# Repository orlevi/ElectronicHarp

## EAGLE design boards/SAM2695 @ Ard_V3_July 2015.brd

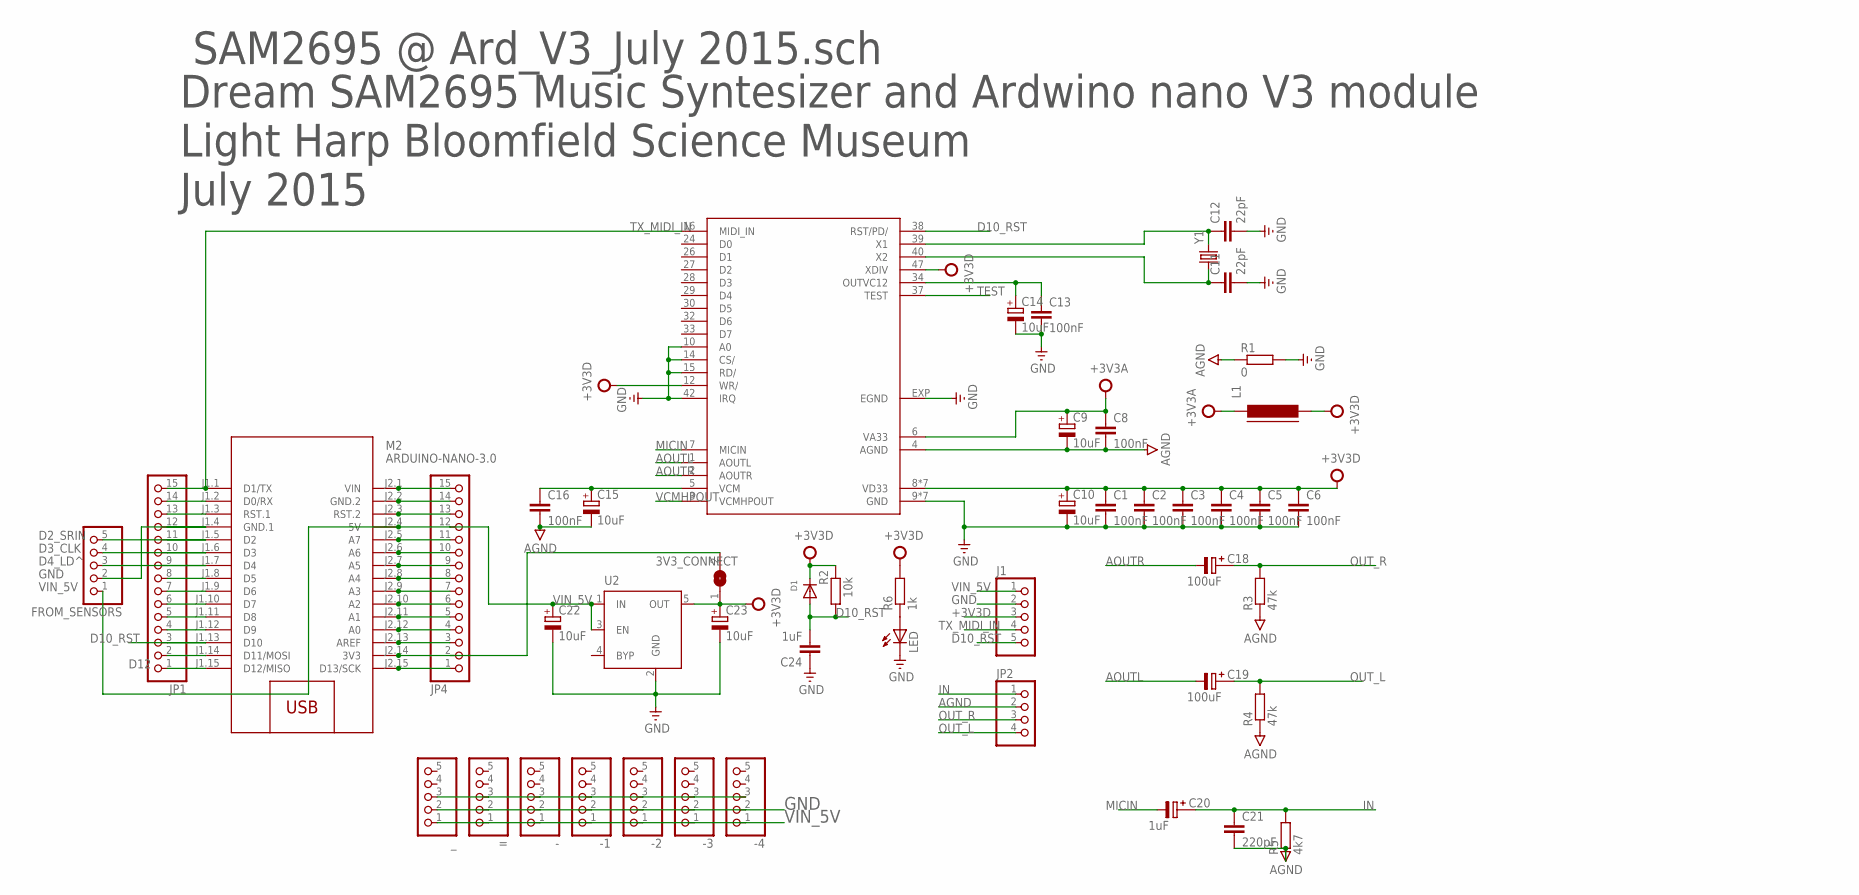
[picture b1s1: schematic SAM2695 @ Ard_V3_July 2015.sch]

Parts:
3V3_CONNECT: SJ
-, -1, -2, -3, -4: PIN_HEAD_1X5_MARKED; 1X5_MARKED
=: PIN_HEAD_1X5_MARKED; 1X5_MARKED
C1, C2, C3, C4, C5, C6, C8, C13, C16: 100nF; C0603K
C9, C10, C14, C15, C22, C23: 10uF; A/3216-18R
C11, C12: 22pF; C0603K
C18, C19: 100uF; SV-B
C20: 1uF; SV-B
C21: 220pF; C0603K
C24: 1uF; C0603
D1: DIODESOD-123; SOD-123
FROM_SENSORS: PIN_HEAD_1X5_MARKED; 1X5_MARKED
J1: PIN_HEAD_1X5_MARKED; 1X5_MARKED
JP1, JP4: PINHD-1X15; 1X15
JP2: HEADER-1X4ROUND; 1X04_ROUND
L1: FERRITE-0603; FB603
LED: LEDCHIP-LED0603; CHIP-LED0603
M2: ARDUINO-NANO-3.0
R1: 0; R0603
R2: 10k; R0603
R3, R4: 47k; R0603
R5: 4k7; R0603
R6: 1k; R0603
U2: MIC5219XX; SOT23-5
U$2: SAM2695LONG_PAD; QFN48_LONG_PAD
Y1: CRYSTALTXC-7A; CRYSTAL-TXC-7A
_: PIN_HEAD_1X5_MARKED; 1X5_MARKED

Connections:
+3V3A: C8.1, C9.+, L1.1, U$2.6 (VA33)
+3V3D: 3V3_CONNECT.1, C1.1, C2.1, C3.1, C4.1, C5.1, C6.1, C10.+, C23.+, D1.C, J1.3, L1.2, R2.2, R6.2, U2.5 (OUT), U$2.8 (VD33), U$2.11 (VD33), U$2.12 (WR/), U$2.20 (VD33), U$2.31 (VD33), U$2.35 (VD33), U$2.41 (VD33), U$2.46 (VD33), U$2.47 (XDIV)
AGND: C8.2, C9.-, C15.-, C16.2, C21.2, JP2.2, R1.1, R3.1, R4.1, R5.1, U$2.4 (AGND)
AOUTL: C19.-, U$2.1 (AOUTL)
AOUTR: C18.-, U$2.2 (AOUTR)
D2_SRIN: FROM_SENSORS.5, JP1.11, M2.J1.5 (D2)
D3_CLK: FROM_SENSORS.4, JP1.10, M2.J1.6 (D3)
D4_LD^: FROM_SENSORS.3, JP1.9, M2.J1.7 (D4)
D5: JP1.8, M2.J1.8 (D5)
D6: JP1.7, M2.J1.9 (D6)
D7: JP1.6, M2.J1.10 (D7)
D8: JP1.5, M2.J1.11 (D8)
D9: JP1.4, M2.J1.12 (D9)
D10_RST: C24.2, D1.A, J1.5, JP1.3, M2.J1.13 (D10), R2.1, U$2.38 (RST/PD/)
D11: JP1.2, M2.J1.14 (D11/MOSI)
D12: JP1.1, M2.J1.15 (D12/MISO)
D13: JP4.1, M2.J2.15 (D13/SCK)
GND: -.2, -1.2, -2.2, -3.2, -4.2, =.2, C1.2, C2.2, C3.2, C4.2, C5.2, C6.2, C10.-, C11.2, C12.2, C13.2, C14.-, C22.-, C23.-, C24.1, FROM_SENSORS.2, J1.2, JP1.12, JP4.14, LED.C, M2.J1.4 (GND.1), M2.J2.2 (GND.2), R1.2, U2.2 (GND), U$2.9 (GND), U$2.10 (A0), U$2.13 (GND), U$2.14 (CS/), U$2.15 (RD/), U$2.18 (GND), U$2.25 (GND), U$2.36 (GND), U$2.42 (IRQ), U$2.45 (GND), U$2.48 (GND), U$2.EXP (EGND), _.2
IN: C20.+, C21.1, JP2.1, R5.2
MICIN: C20.-, U$2.7 (MICIN)
unnamed: -.3, -1.3, -2.3, -3.3, -4.3, =.3, _.3
unnamed: C13.1, C14.+, U$2.34 (OUTVC12)
unnamed: C12.1, U$2.39 (X1), Y1.P$2 (2)
unnamed: C11.1, U$2.40 (X2), Y1.P$1 (1)
unnamed: LED.A, R6.1
unnamed: C15.+, C16.1, U$2.5 (VCM)
unnamed: 3V3_CONNECT.2, JP4.2, M2.J2.14 (3V3)
unnamed: JP4.3, M2.J2.13 (AREF)
unnamed: JP4.4, M2.J2.12 (A0)
unnamed: JP4.5, M2.J2.11 (A1)
unnamed: JP4.6, M2.J2.10 (A2)
unnamed: JP4.7, M2.J2.9 (A3)
unnamed: JP4.8, M2.J2.8 (A4)
unnamed: JP4.9, M2.J2.7 (A5)
unnamed: JP4.10, M2.J2.6 (A6)
unnamed: JP4.11, M2.J2.5 (A7)
unnamed: JP4.15, M2.J2.1 (VIN)
OUT_L: C19.+, JP2.4, R4.2
OUT_R: C18.+, JP2.3, R3.2
RST1_ARD: JP1.13, M2.J1.3 (RST.1)
RST2_ARD: JP4.13, M2.J2.3 (RST.2)
RX: JP1.14, M2.J1.2 (D0/RX)
TEST: U$2.37 (TEST)
TX_MIDI_IN: J1.4, JP1.15, M2.J1.1 (D1/TX), U$2.16 (MIDI_IN)
VCMHPOUT: U$2.3 (VCMHPOUT)
VIN_5V: -.1, -1.1, -2.1, -3.1, -4.1, =.1, C22.+, FROM_SENSORS.1, J1.1, JP4.12, M2.J2.4 (5V), U2.1 (IN), U2.3 (EN), _.1

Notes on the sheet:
SAM2695 @ Ard_V3_July 2015.sch
Dream SAM2695 Music Syntesizer and Ardwino nano V3 module Light Harp Bloomfield Science Museum July 2015

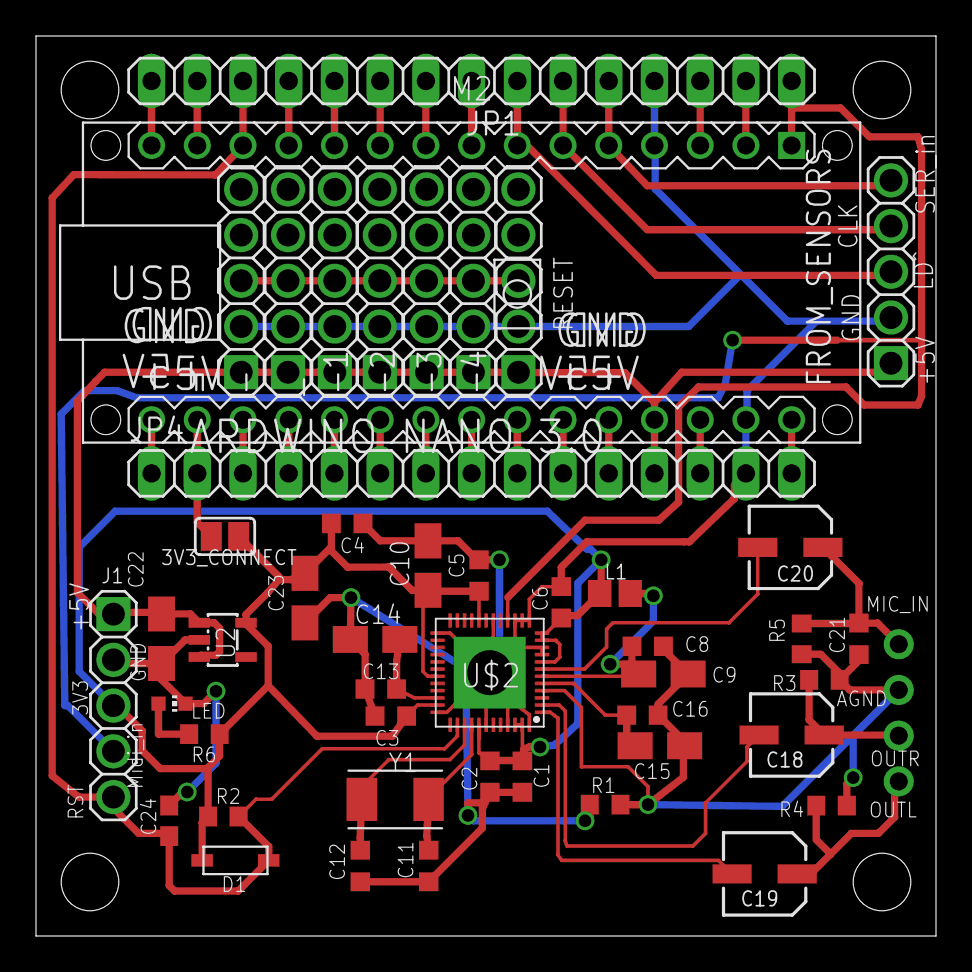
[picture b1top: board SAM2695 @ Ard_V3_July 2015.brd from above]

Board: 2 copper layers, 50.0 x 50.0 mm, 48 parts (0 on the bottom side), 44 nets.

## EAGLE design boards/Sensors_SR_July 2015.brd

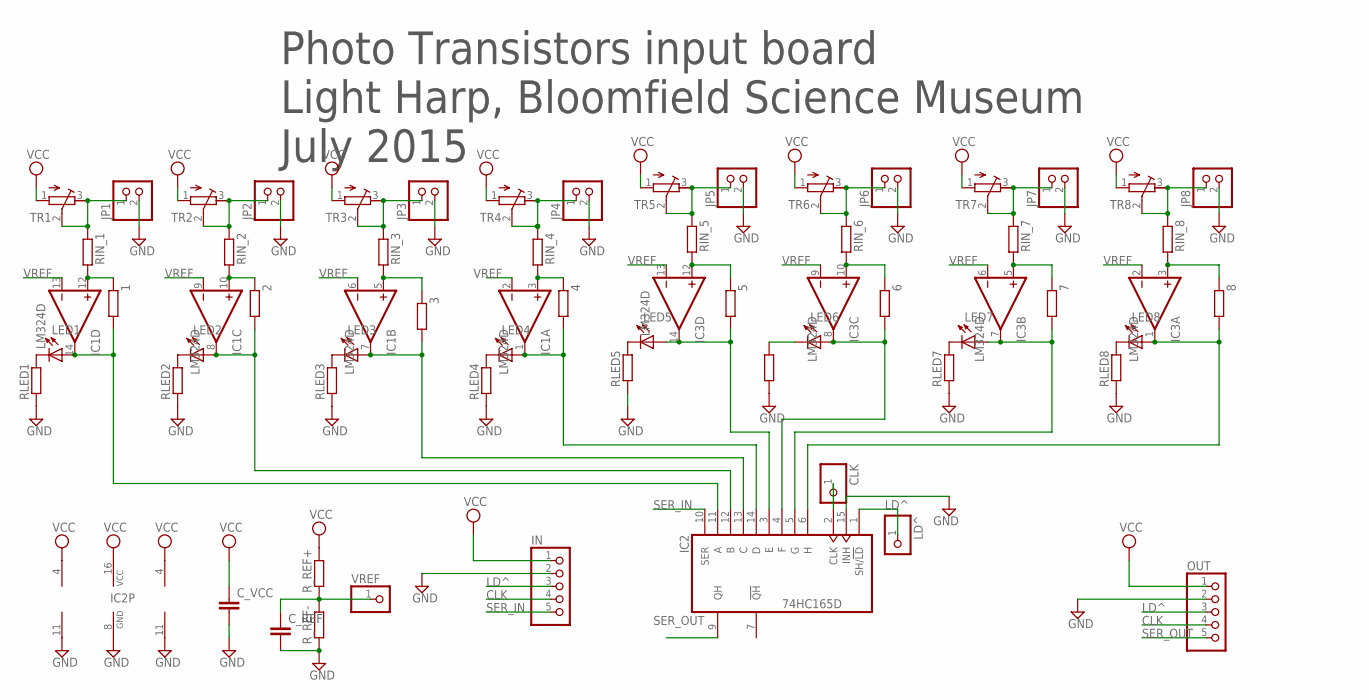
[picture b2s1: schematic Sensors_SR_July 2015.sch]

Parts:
1, 2, 3, 4, 5, 6, 7, 8: R-EU_R0603; R0603
CLK: PINHD-1X1; 1X01
C_REF: C-EUC0603; C0603
C_VCC: C-EUC0805; C0805
IC1, IC3: LM324D; SO14
IC2: 74HC165D; SO16
IN: PIN_HEAD_1X5_MARKED; 1X5_MARKED
JP1, JP2, JP3, JP4, JP5, JP6, JP7, JP8: PINHD-1X2SQ&RND; 1X02_SQ&ROUND
LD^: PINHD-1X1; 1X01
LED1, LED2, LED3, LED4, LED5, LED6, LED7, LED8: LEDCHIPLED_0805; CHIPLED_0805
OUT: PIN_HEAD_1X5_MARKED; 1X5_MARKED
RIN_1, RIN_2, RIN_3, RIN_4, RIN_5, RIN_6, RIN_7, RIN_8: R-EU_R0603; R0603
RLED1, RLED2, RLED3, RLED4, RLED5, RLED6, RLED7, RLED8: R-EU_R0603; R0603
R_REF+: R-EU_R0603; R0603
R_REF-: R-EU_R0603; R0603
TR1, TR2, TR3, TR4, TR5, TR6, TR7, TR8: R-TRIMM64W_W; RTRIM64W_W
VREF: PINHD-1X1; 1X01

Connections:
CLK: CLK.1, IC2.2 (CLK), IN.4, OUT.4
GND: C_REF.2, C_VCC.2, IC1.11 (V-), IC2.8 (GND), IC2.15 (INH), IC3.11 (V-), IN.2, JP1.2, JP2.2, JP3.2, JP4.2, JP5.2, JP6.2, JP7.2, JP8.2, OUT.2, RLED1.1, RLED2.1, RLED3.1, RLED4.1, RLED5.1, RLED6.1, RLED7.1, RLED8.1, R_REF-.1
LD^: IC2.1 (SH/!LD), IN.3, LD^.1, OUT.3
unnamed: 1.2, IC1.14 (OUT), IC2.11 (A), LED1.A
unnamed: 1.1, IC1.12 (+IN), RIN_1.2
unnamed: LED1.C, RLED1.2
unnamed: JP1.1, RIN_1.1, TR1.2 (S), TR1.3 (A)
unnamed: JP2.1, RIN_2.1, TR2.2 (S), TR2.3 (A)
unnamed: JP3.1, RIN_3.1, TR3.2 (S), TR3.3 (A)
unnamed: JP4.1, RIN_4.1, TR4.2 (S), TR4.3 (A)
unnamed: JP5.1, RIN_5.1, TR5.2 (S), TR5.3 (A)
unnamed: JP6.1, RIN_6.1, TR6.2 (S), TR6.3 (A)
unnamed: JP7.1, RIN_7.1, TR7.2 (S), TR7.3 (A)
unnamed: JP8.1, RIN_8.1, TR8.2 (S), TR8.3 (A)
unnamed: 2.2, IC1.8 (OUT), IC2.12 (B), LED2.A
unnamed: 2.1, IC1.10 (+IN), RIN_2.2
unnamed: LED2.C, RLED2.2
unnamed: 3.1, IC1.5 (+IN), RIN_3.2
unnamed: 3.2, IC1.7 (OUT), IC2.13 (C), LED3.A
unnamed: 4.2, IC1.1 (OUT), IC2.14 (D), LED4.A
unnamed: 4.1, IC1.3 (+IN), RIN_4.2
unnamed: LED5.C, RLED5.2
unnamed: LED4.C, RLED4.2
unnamed: 5.1, IC3.12 (+IN), RIN_5.2
unnamed: 5.2, IC2.3 (E), IC3.14 (OUT), LED5.A
unnamed: 6.2, IC2.4 (F), IC3.8 (OUT), LED6.A
unnamed: 6.1, IC3.10 (+IN), RIN_6.2
unnamed: 7.2, IC2.5 (G), IC3.7 (OUT), LED7.A
unnamed: LED6.C, RLED6.2
unnamed: LED3.C, RLED3.2
unnamed: LED7.C, RLED7.2
unnamed: 7.1, IC3.5 (+IN), RIN_7.2
unnamed: 8.2, IC2.6 (H), IC3.1 (OUT), LED8.A
unnamed: LED8.C, RLED8.2
unnamed: 8.1, IC3.3 (+IN), RIN_8.2
SER_IN: IC2.10 (SER), IN.5
SER_OUT: IC2.9 (QH), OUT.5
VCC: C_VCC.1, IC1.4 (V+), IC2.16 (VCC), IC3.4 (V+), IN.1, OUT.1, R_REF+.2, TR1.1 (E), TR2.1 (E), TR3.1 (E), TR4.1 (E), TR5.1 (E), TR6.1 (E), TR7.1 (E), TR8.1 (E)
VREF: C_REF.1, IC1.2 (-IN), IC1.6 (-IN), IC1.9 (-IN), IC1.13 (-IN), IC3.2 (-IN), IC3.6 (-IN), IC3.9 (-IN), IC3.13 (-IN), R_REF+.1, R_REF-.2, VREF.1

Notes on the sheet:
Photo Transistors input board Light Harp, Bloomfield Science Museum July 2015

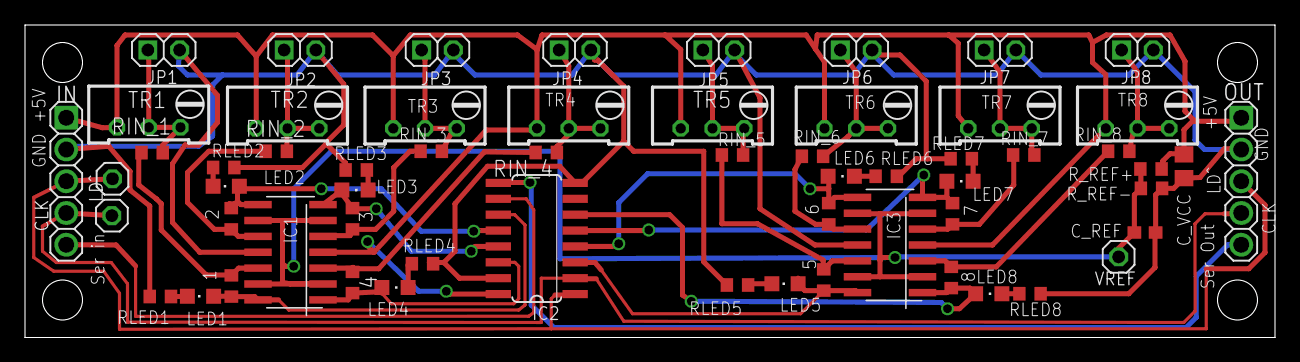
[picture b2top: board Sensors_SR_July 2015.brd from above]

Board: 2 copper layers, 100.0 x 25.0 mm, 60 parts (0 on the bottom side), 39 nets.

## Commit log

2015-08-13 added arduino midi generator
2015-08-13 added boards layouts and schematics
2015-08-20 added datasheets and updated midi player
2015-09-24 shift register + midi player work
2015-10-15 updated to 3 shift registers, key table to better suit a harp
2015-10-15 implemented PWM for lasers
2015-10-26 implemented volume change, and children eye burning mechanism
2015-11-19 added button to work only with half of the notes
2015-11-25 notes pushed up by 1+ octaves, volume is also set in the setup phase
2015-12-04 added sam2695 datasheet, implemented little Yoni easterEgg
2015-12-04 ok, hope now the merge is really done, it compiles in my computer but beware that maybe i busted something in the process...
2016-10-27 song played on low volume
2016-10-27 added debouncsing in sensor reading, lowered a little the volume

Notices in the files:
parts and their libraries:
SparkFun-FreqCtrl: Licensing: Creative Commons ShareAlike 4.0 International - https://creativecommons.org/licenses/by-sa/4.0
microbuilder: This work is placed in the public domain, and may be freely used for commercial and non-commercial work with the following conditions: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
